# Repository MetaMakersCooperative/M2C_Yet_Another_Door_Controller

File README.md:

# M2C Yet Another Door Controller

Proof of concept for new door controller design using a `WT32-ETH01`.

## Development Requirements

Make sure version `v1.X` of the Arduino IDE installed. It is required to upload the cards file. See [Cards File](#cards_file) section.

`arduino-cli` also needs to be installed to compile and upload the sketch. It is possible to use the Arduino IDE `v1.X` or `v2` but they have not been tested/verified. Milage may vary.

## Cards File

The sketch assumes a file named `cards.txt` exists within a `LitteFS` file system. The code will not function correctly without it.

Unfortunately, the only way to upload the file to the device is using `v1.X` Arduino IDE. This is because the upload using a plugin that only can be used with that version of the IDE. Setting up the upload plugin is only required if the `cards.txt` file needs to be updated or if the flash storage was wiped.

### Setup the Upload Plugin

To setup the plugin, follow the steps outlined below:

1. First download the following `zip` file: [https://github.com/lorol/arduino-esp32fs-plugin/releases/download/2.0.7/esp32fs.zip](https://github.com/lorol/arduino-esp32fs-plugin/releases/download/2.0.7/esp32fs.zip)
2. Unzip and place the `esp32fs.jar` file in the following directory: `~/Arduino/tools/ESP32FS/tool/esp32fs.jar`
3. Restart Arduino IDE if it's running

### Uploading

Before uploading, create the `data` directory in the project root if it does not already exist. Update/create the `card.txt` file with the codes that should unlock the door. Make sure each code is in it's own line, like below:

> Each code should be no more than 10 digits long and only container digits `0-9`. No leading zeros!

```text
1234567
8912345
6789123
```

Double check and make sure the project structure matches the following:

```text
~/Arduino/M2C_Yet_Another_Door_Controller/
├── data
│   └── cards.txt
├── README.md
├── sketch.yaml
└── M2C_Yet_Another_Door_Controller.ino
```

To upload the `card.txt` file, follow the steps outlined below:

> When referencing the Arduino IDE, it is implied that it's `v1.X` not `v2`

1. Open Arduino IDE and open the `M2CYetAnotherDoorController.ino` sketch.
2. Navigate and click on `Tools -> Board` and select `WT32-ETH01 Ethernet Module` if it is not already selected.
3. Navigate and click on `Tools -> ESP32 Sketch Date Upload`
4. Select `LittleFS` then click `OK`

## Libraries

To install the `esp32` libraries run the following command:

```bash
arduino-cli core install esp32:esp32@3.0.2
```

> Might need to run `arduino-cli core update-index` to update the board index.

This will install [espressif/arduino-esp32 version `3.0.2`](https://github.com/espressif/arduino-esp32/tree/3.0.2).

The following libraries can be installed using the Arduino IDE or by downloading the files directly from the source repositories.

When downloading the libraries manually, make sure the source is place them within the following directory: `~/Arduino/libraries`.

The `libraries` should look like this assuming the only installed libraries are the ones used by this project.

```
~/Arduino/libraries
├── LinkedList
│   ├── ...
└── Yet_Another_Arduino_Wiegand_Library
    ├── ...
```

> Make sure to download the source tagged with the versions listed below!

The following dependencies need to be installed manually as the latest versions are required:

> The best way to get these libraries is to `git clone` them into the `~/Arduino/libraries` directory.

- [Yet Another Arduino Wiegand Library](https://github.com/paulo-raca/YetAnotherArduinoWiegandLibrary) commit: `556e7b8` tag: `2.0.1`
- [LinkedList](https://github.com/ivanseidel/LinkedList) commit: `0439a72` tag: `v1.3.3`
- [espMqttClient](https://github.com/bertmelis/espMqttClient) commit: `70d3113` tag: `v1.7.0`
- [AsyncTCP](https://github.com/mathieucarbou/AsyncTCP) commit: `b20e92e` tag: `v3.1.4`

> AsyncTCP is still required even though it's not being used

## Commands (using CLI)

> Note: `/dev/ttyUSB0` is the default device. Run the following command to see what device is being used: `arduino-cli board list`. Make sure to modify the commands below to match that device.

To compile the sketch with defaults, run following command:

> WARNING: Defaults will apply not overridden which could cause a lot of problems on multi door deployments. See the [Override Defaults](#override-defaults) section below.

```bash
arduino-cli compile --fqbn esp32:esp32:wt32-eth01 ./
```

To enable more debugging messages, run the following command:

```bash
arduino-cli compile --build-property "build.extra_flags=\"-DDC_DEBUG=1\"" --clean --fqbn esp32:esp32:wt32-eth01 ./
```

To Upload the compiled sketch:

```bash
arduino-cli upload -p /dev/ttyUSB0 --fqbn esp32:esp32:wt32-eth01 ./
```

To monitor the serial output:

```bash
arduino-cli monitor --log-level debug --fqbn esp32:esp32:wt32-eth01 -p /dev/ttyUSB0 -c baudrate=115200
```
## MQTT Broker

> NOTE: The code assumes the MQTT server connection is TLS. Only TLS v1.2 is supported. Using TLS v1.3 will result in some weird errors. 

The device will send logs, lock, unlock, and other events to the configured MQTT broker. If disconnected, only a few messages will be queued and sent when it's able to reconnect.

If the `door_controller/access_list` topic is received, the device will replace the card file with the payload, then attempt to reload the list from the updated file.

The device will also respond to messages with the `door_controller/health_check` topic. This is designed to help with monitoring the healthiness of the device.

### `root_ca.h`

Use the example file, `root_ca.h.example`, to create the `root_ca.h` file containing the root certificate for the MQTT broker.

> NOTE: The root certificate will expire at some point so make sure you mark it in your calendar!

If you're using Let's Encrypt, then there is a good chance that the root certificate can be download from the following URL: [letsencrypt.org/certs/isrgrootx1.pem](https://letsencrypt.org/certs/isrgrootx1.pem)

Otherwise, check out [letsencrypt.org/certificates/](https://letsencrypt.org/certificates/) for a complete list.

## Override Defaults

> Note: Make sure the latest Arduino CLI is installed

The table below shows the build flags that should be overridden for each controller being deployed.
Refer to the source files for a complete list of overridable flags.

| Flag Name    | Default             | Description                                                                                                                           | Build Argument                     |
|--------------|---------------------|---------------------------------------------------------------------------------------------------------------------------------------|------------------------------------|
| DC_HOST_NAME | m2cdoorone          | The value that will be set as the device's host name                                                                                  | -DDC_HOST_NAME=m2cdoorone          |
| DC_CLIENT_ID | door_one            | Client ID is used by the MQTT broker to identify the client. This value needs to be unique across all clients connected to the broker | -DDC_CLIENT_ID=door_one            |
| DC_MQTT_HOST | mqtt.metamakers.org | Host name for the MQTT Broker. The host name is used to get the server IP using DNS                                                   | -DDC_MQTT_HOST=mqtt.metamakers.org |
| DC_MQTT_USER | door_one            | The user that the MQTT client will use to authenticate                                                                                | -DDC_MQTT_USER=door_one            |
| DC_MQTT_PW   | Door_One!1          | The password that the MQTT client will use to authenticate                                                                            | -DDC_MQTT_PW=Door_One!1            |
| DC_NTP_HOST  | pool.ntp.org        | The domain used to update the RTC using NTP                                                                                           | -DDC_NTP_HOST=pool.ntp.org         |
| DC_DEBUG     | 0                   | Enable more verbose debugging information via the serial port. Do not enable this for production deployments                          | -DDC_DEBUG=0                       |

Below is an example of how to override all the flags in the table above:

> Documentation on the CLI compile command can be found [here](https://arduino.github.io/arduino-cli/1.0/commands/arduino-cli_compile/).

```bash
arduino-cli compile --build-property "build.extra_flags=-DDC_DEBUG=0 \"-DDC_HOST_NAME=\"m2cdoorone\"\" \"-DDC_CLIENT_ID=\"door_one\"\" \"-DDC_MQTT_HOST=\"mqtt.metamakers.org\"\" \"-DDC_MQTT_USER=\"door_one\"\" \"-DDC_MQTT_PW=\"Door_One!1\"\" \"-DDC_NTP_HOST=\"pool.ntp.org\"\"" --clean --fqbn esp32:esp32:wt32-eth01 ./
```

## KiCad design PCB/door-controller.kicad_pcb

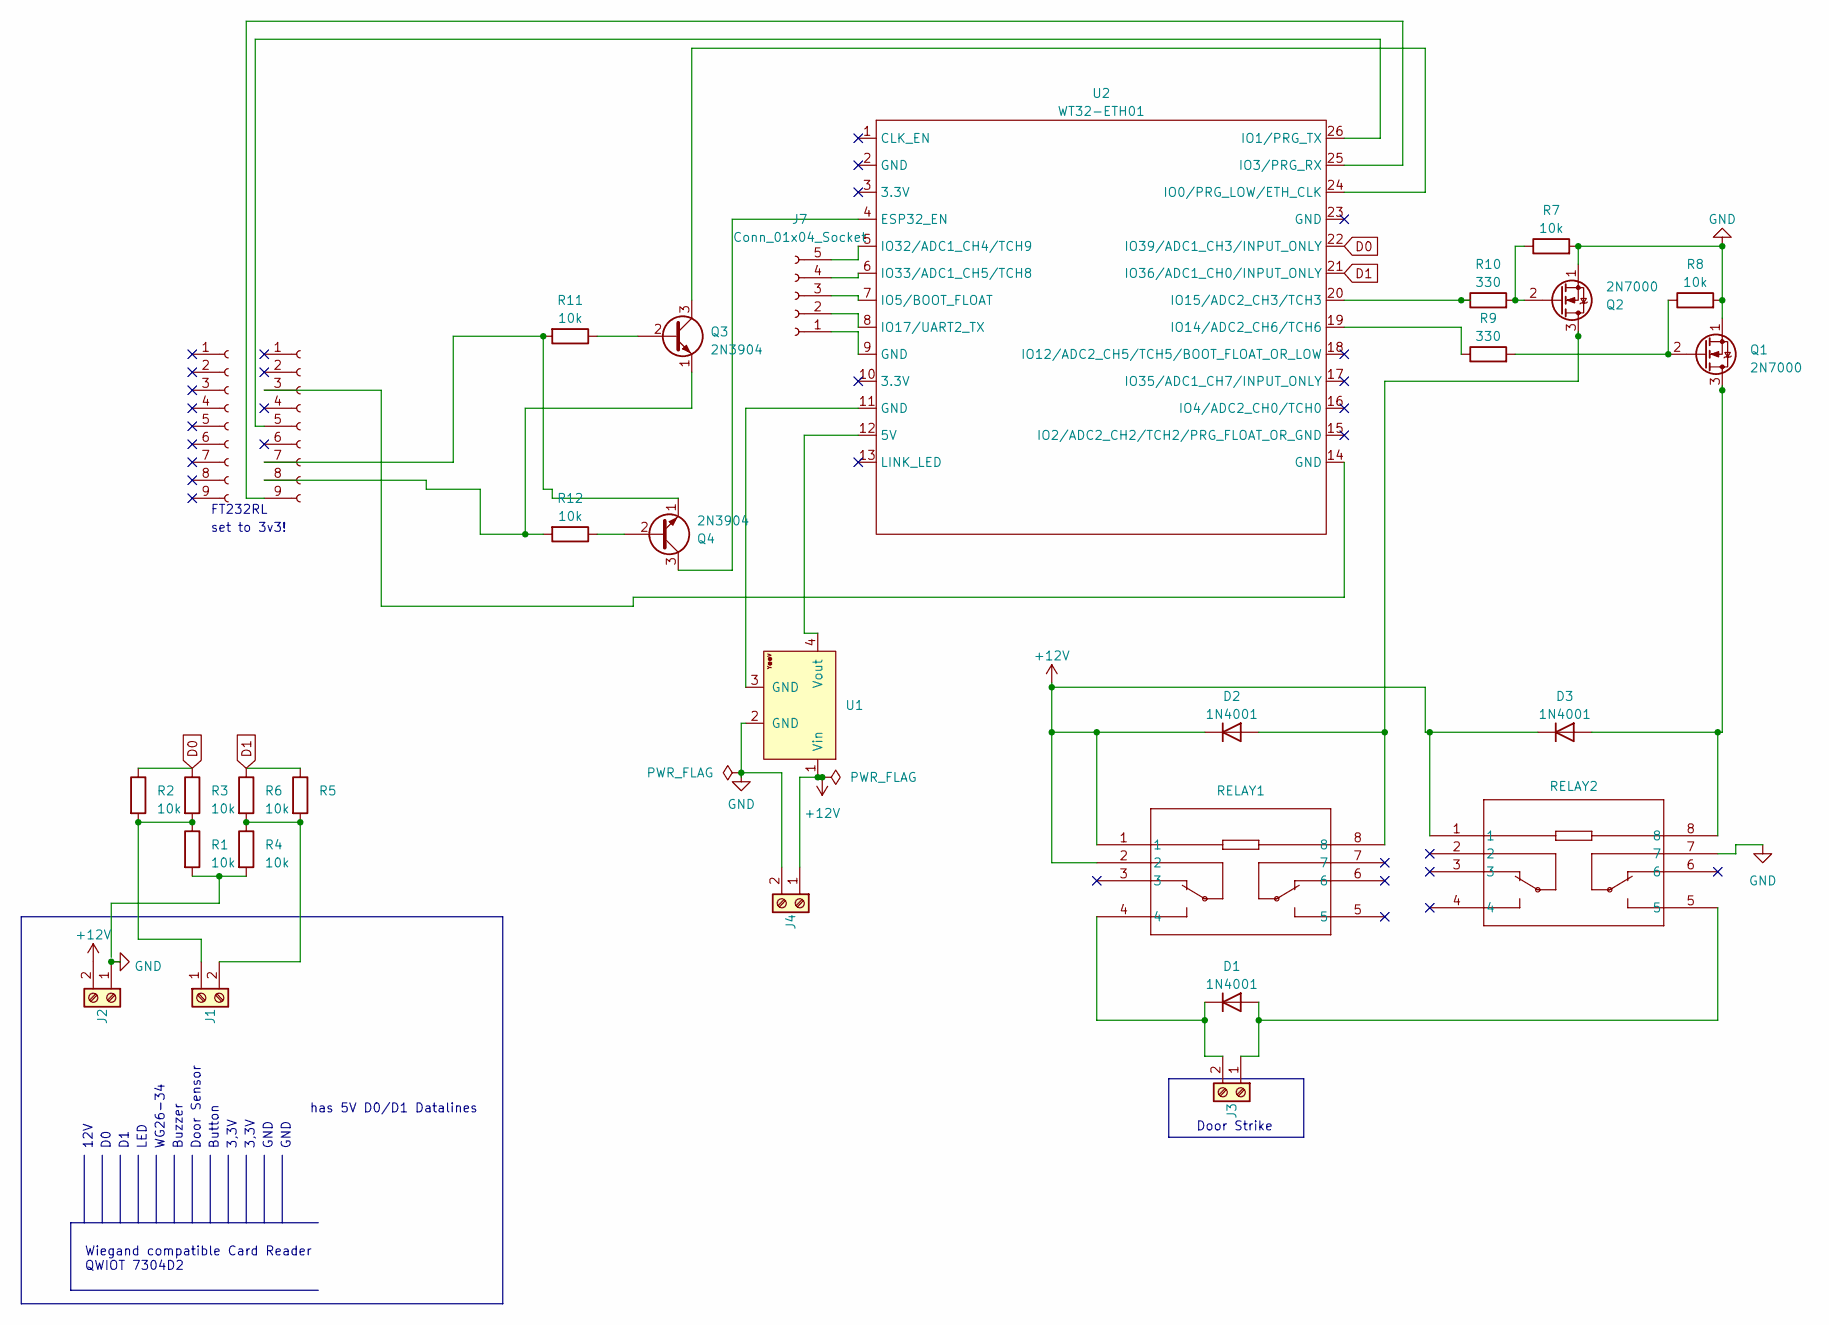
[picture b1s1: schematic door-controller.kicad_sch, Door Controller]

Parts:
D1, D2, D3: 1N4001; D_DO-41_SOD81_P10.16mm_Horizontal
J1, J2, J3, J4: TerminalBlock_Phoenix_MKDS-1,5-2_1x02_P5.00mm_Horizontal
J5, J6: Conn_01x09_Socket; PinSocket_1x09_P2.54mm_Vertical
J7: Conn_01x04_Socket; PinSocket_1x05_P2.54mm_Vertical
Q1, Q2: 2N7000; TO-92_Inline
Q3, Q4: 2N3904; TO-92_Inline
R1, R2, R3, R4, R5, R6, R7, R8, R11, R12: 10k; R_Axial_DIN0204_L3.6mm_D1.6mm_P7.62mm_Horizontal
R9, R10: 330; R_Axial_DIN0204_L3.6mm_D1.6mm_P7.62mm_Horizontal
RELAY1, RELAY2: RELAY8_J104D2C12VDC.20S_CRS
U1: YAAJ_DCDC_StepDown_LM2596; YAAJ_DCDC_StepDown_LM2596_Universal
U2: WT32-ETH01

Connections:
+12V: D2.1 (K), D3.1 (K), J2.2, J4.1, RELAY1.1, RELAY1.2, RELAY2.1, U1.1 (Vin)
D0: R2.1, R3.1, U2.22 (IO39/ADC1_CH3/INPUT_ONLY)
D1: R5.1, R6.1, U2.21 (IO36/ADC1_CH0/INPUT_ONLY)
GND: J2.1, J4.2, Q1.1 (S), Q2.1 (S), R7.2, R8.2, RELAY2.7, U1.2 (GND)
unnamed: D1.2 (A), J3.1, RELAY2.5
unnamed: D1.1 (K), J3.2, RELAY1.4
unnamed: D2.2 (A), Q2.3 (D), RELAY1.8
unnamed: D3.2 (A), Q1.3 (D), RELAY2.8
unnamed: J1.1, R1.1, R2.2, R3.2
unnamed: J1.2, R4.1, R5.2, R6.2
unnamed: J6.3, U2.14 (GND)
unnamed: J6.5, U2.26 (IO1/PRG_TX)
unnamed: J6.7, Q4.1 (E), R11.2
unnamed: J6.8, Q3.1 (E), R12.2
unnamed: J6.9, U2.25 (IO3/PRG_RX)
unnamed: J7.1, U2.9 (GND)
unnamed: J7.2, U2.8 (IO17/UART2_TX)
unnamed: J7.3, U2.7 (IO5/BOOT_FLOAT)
unnamed: J7.4, U2.6 (IO33/ADC1_CH5/TCH8)
unnamed: J7.5, U2.5 (IO32/ADC1_CH4/TCH9)
unnamed: Q1.2 (G), R8.1, R9.2
unnamed: Q2.2 (G), R7.1, R10.2
unnamed: Q3.2 (B), R11.1
unnamed: Q3.3 (C), U2.24 (IO0/PRG_LOW/ETH_CLK)
unnamed: Q4.2 (B), R12.1
unnamed: Q4.3 (C), U2.4 (ESP32_EN)
unnamed: R1.2, R4.2
unnamed: U1.3 (GND), U2.11 (GND)
unnamed: U1.4 (Vout), U2.12 (5V)
unnamed: R9.1, U2.19 (IO14/ADC2_CH6/TCH6)
unnamed: R10.1, U2.20 (IO15/ADC2_CH3/TCH3)

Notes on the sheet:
12V
3,3V
Door Strike
Buzzer
WG26-34
Button
GND
FT232RL
has 5V D0/D1 Datalines
Wiegand compatible Card Reader QWIOT 7304D2
Door Sensor
LED
GND
set to 3v3!

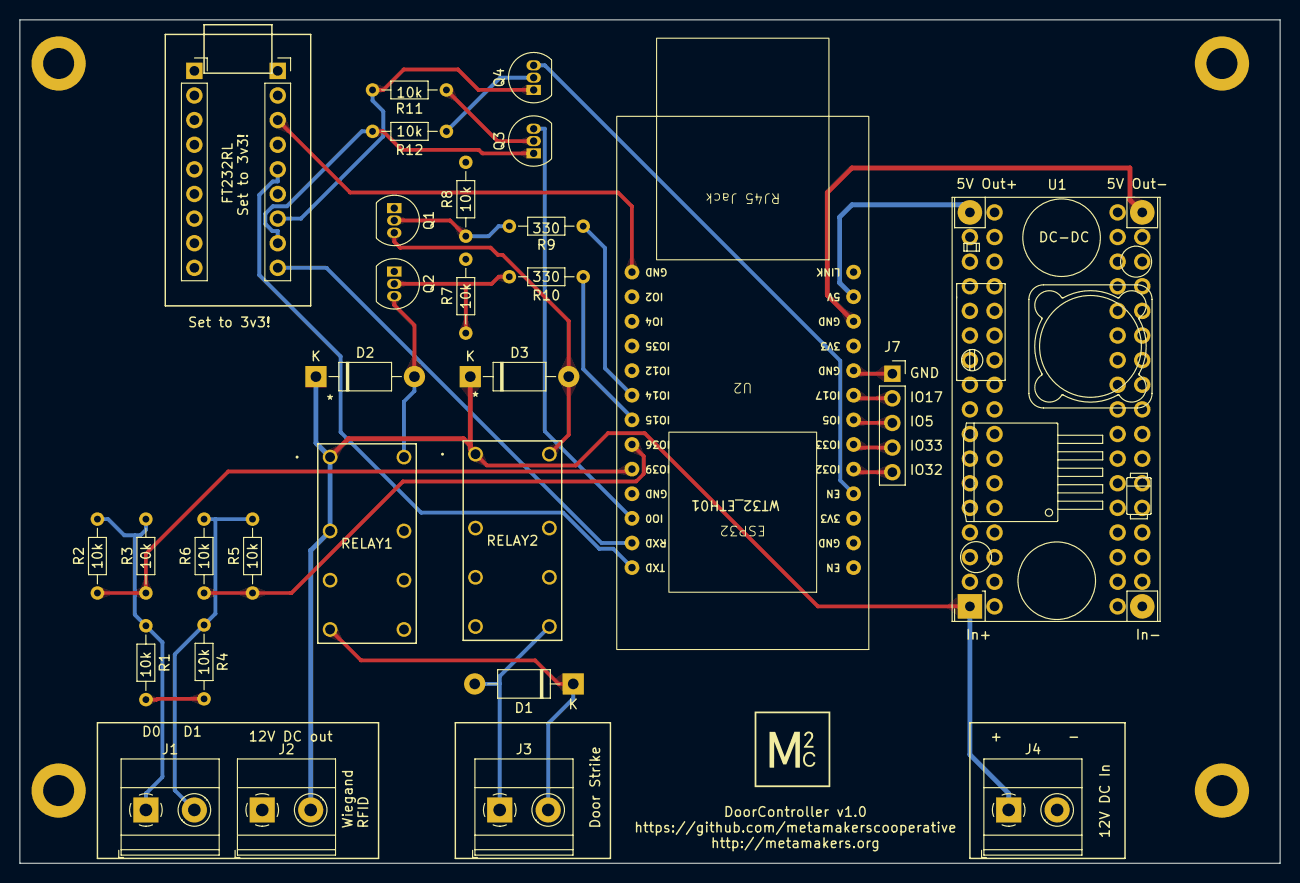
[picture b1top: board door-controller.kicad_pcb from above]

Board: 2 copper layers, 130.0 x 87.0 mm, 34 parts (0 on the bottom side), 31 nets.

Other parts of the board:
MH1, MH2, MH3, MH4: MountingHole_3.2mm_M3_DIN965_Pad

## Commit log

2023-12-29 Add files via upload
    add schematic pdf
2023-12-29 add schematic as kicad_sch and pdf
2024-01-14 add pcb design files
2024-03-24 Rename file so that arduino-cli stops complaining
2024-03-25 Add new dependencies and documentation
    Going to use espMqttClient and AsyncTPC libraries to build a POC.
2024-06-27 Update README.md
    include location of config file
2024-07-03 attribution for Linked List
2024-07-27 Change a few log messages to be a bit more descriptive
2024-07-27 QoS and topic structure changes
    Use the client id as part of the publish topic. This will make it
    possible to know what client the messsage came from. Otherwise, the
    client id would have to be placed into every payload
    Update QoS from 2 to 1. 2 is pretty chatty and 1 still provides the
    reliability we want. Also updated the code to handle duplicates which
    are not possible when using QoS 1 over 2
2024-07-27 Testing out reseting NTP
2024-07-27 Zero out card code if the code was denied access
2024-07-27 Configurable NTP host and more logging
    Make NTP host a build argument.
    Add better logging over mqtt by using more descriptive topics.
    Add more logging of information to help debug any issues.
    Add code to throw out multipart payloads as we don't have the ability to
    handle those kinds of payloads at the moment.
2024-07-27 Working on documentation
2024-07-27 MQTT Proof of concept
    The goals where to be able to send logs, unlock/deny, and health check
    events to a MQTT broker. Also being able process a new card list by
    subscribing to the access_list topic. This allows for updating the
    cards.txt file without having to plug a laptop into the door controller.
    This change also includes all the plumbing for setting up the ETH
    connection and getting the MQTT broker IP using a DNS lookup.
2024-07-27 Update dependencies and README to recommend downloading them using git
2024-07-27 Added root ca example
2024-07-27 Finished Testing Door Controller
    - Updated the code base to use arduino-esp32 version 3.0.2
    - Change MQTT from the async to secure client so that it would be
    possible to connect to the MQTT server using TLS
    - Added root_ca.h header
    - Changed MQTT client timeout from 2 to 5 seconds
    - Fixed snprintf string formatting issues
2024-08-06 Fixed issues with card list file
    - Removed the line adding EOF to the end of the file. This is not needed
    and results in a 0xFF being inserted at the end of the file which
    causes some issues if the last code isn't followed by a new line.
    - Refactored a few variable names to help with readability
    - Added in more debug print statements
    - Changed the code that takes the payload and copies it to the card list
